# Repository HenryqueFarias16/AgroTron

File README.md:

# AgroTron
Projeto de Automação agrícola com microcontrolador ESP12-E

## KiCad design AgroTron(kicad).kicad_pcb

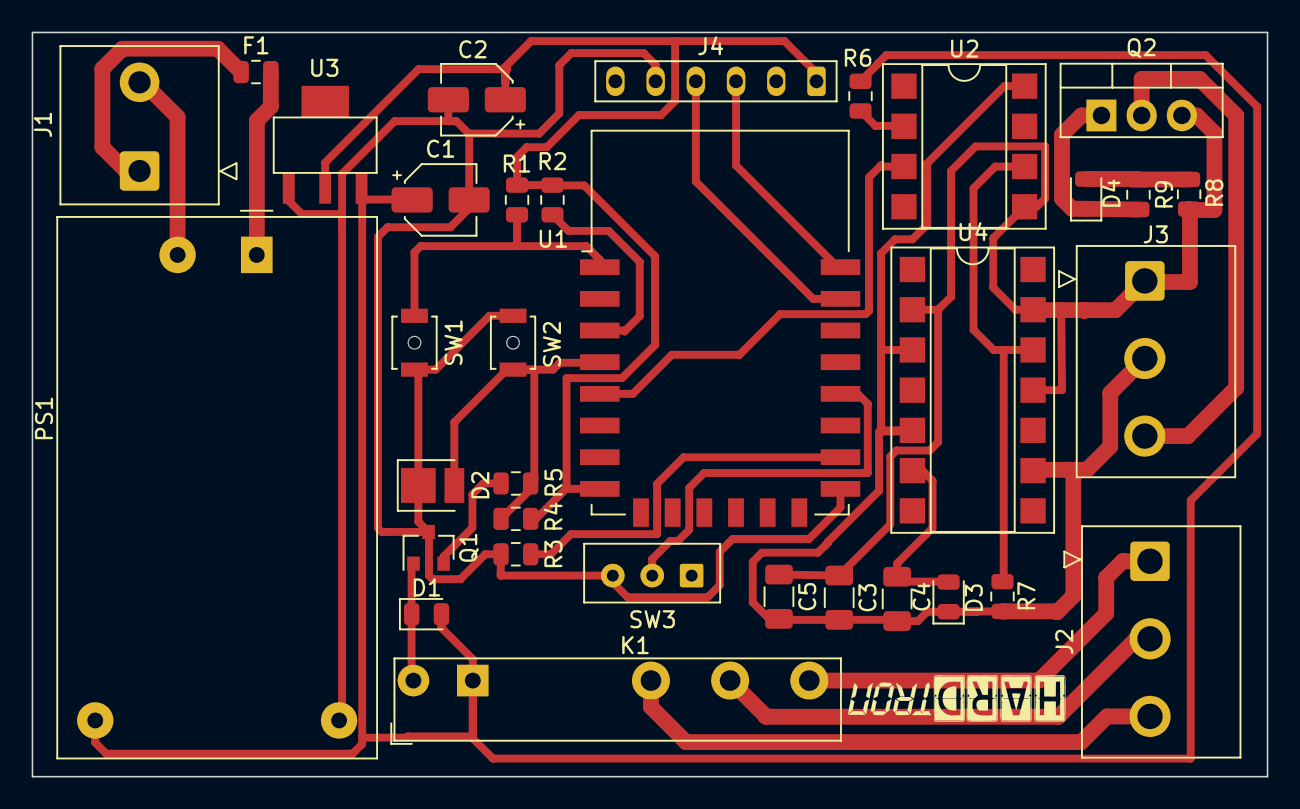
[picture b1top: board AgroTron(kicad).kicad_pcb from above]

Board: 2 copper layers, 78.0 x 47.0 mm, 34 parts (0 on the bottom side), 27 nets.

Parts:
C1, C2: 10uF; CP_Elec_4x5.4
C3, C4, C5: 1uF; C_1206_3216Metric
D1, D3, D4: DIODE; D_0805_2012Metric
D2: LED; LED_PLCC_2835
F1: 1A; Fuse_0805_2012Metric
J1: InAC; Tblock10x10mm
J2, J3: 300V/10A; Tblock3.10x10mm
J4: Cp2102; Wuerth_WR-WTB_64800611622_1x06_P2.50mm_Vertical
K1: FINDER-34.51; Relay_SPDT_Finder_34.51_Vertical
PS1: HLK-PM01; Converter_ACDC_HiLink_HLK-PMxx
Q1: BC547; SOT-23
Q2: IRF1404ZPBF; TO-220-3_Vertical
R1, R3, R4, R7, R8: 10k; R_0805_2012Metric
R2: 10K; R_0805_2012Metric
R5, R9: 1k; R_0805_2012Metric
R6: 330; R_0805_2012Metric
SW1, SW2: TS-1102-5016; SW_SPST_B3U-1000P-B
SW3: SS12D00; TE_826576-3_1x03_P1mm_Vertical
U1: ESP-12E
U2: 6N135; DIP-8_W7.62mm_SMDSocket_SmallPads
U3: LM1117-3.3; R-PDSO-G4
U4: IR2110; DIP-14_W7.62mm_SMDSocket_SmallPads

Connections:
+3V3: C2.1, J4.1, R1.2, R2.2, R4.2, U1.8, U3.2
+5V: C1.1, D1.2, K1.A1, PS1.4, R6.1, U3.3
+12V: C3.2, C4.1, C5.2, D3.1, J3.2, R7.1, U2.8, U4.3, U4.5, U4.9
C: J2.2, K1.11
EN: R2.1, U1.3
Fase: F1.1, J1.1
Fusivel: F1.2, PS1.1
GND: C1.2, C2.2, D2.1, J4.5, PS1.3, Q1.3, R3.1, SW1.2, SW2.2, SW3.3, U1.15, U3.1
GndOut: C3.1, C5.1, J3.1, Q2.3, R8.1, U2.5, U4.2, U4.11, U4.13
Gpio0: SW3.2, U1.18
Gpio14: U1.5, U2.3
Gpio15: R3.2, U1.16
Gpio16: D2.2, R4.1, R5.1, SW2.1, U1.4
Na: J2.1, K1.14
NegBomba: J3.3, Q2.2
unnamed: C4.2, D3.2, U4.6
unnamed: D1.1, K1.A2, Q1.1
unnamed: D4.1, Q2.1, R9.2
unnamed: D4.2, R8.2, R9.1
unnamed: Q1.2, R5.2
unnamed: R6.2, U2.2
Neutro: J1.2, PS1.2
Nf: J2.3, K1.12
Output: R7.2, U2.6, U4.12
Rst: R1.1, SW1.1, U1.1
Rx: J4.4, U1.21
Tx: J4.3, U1.22
